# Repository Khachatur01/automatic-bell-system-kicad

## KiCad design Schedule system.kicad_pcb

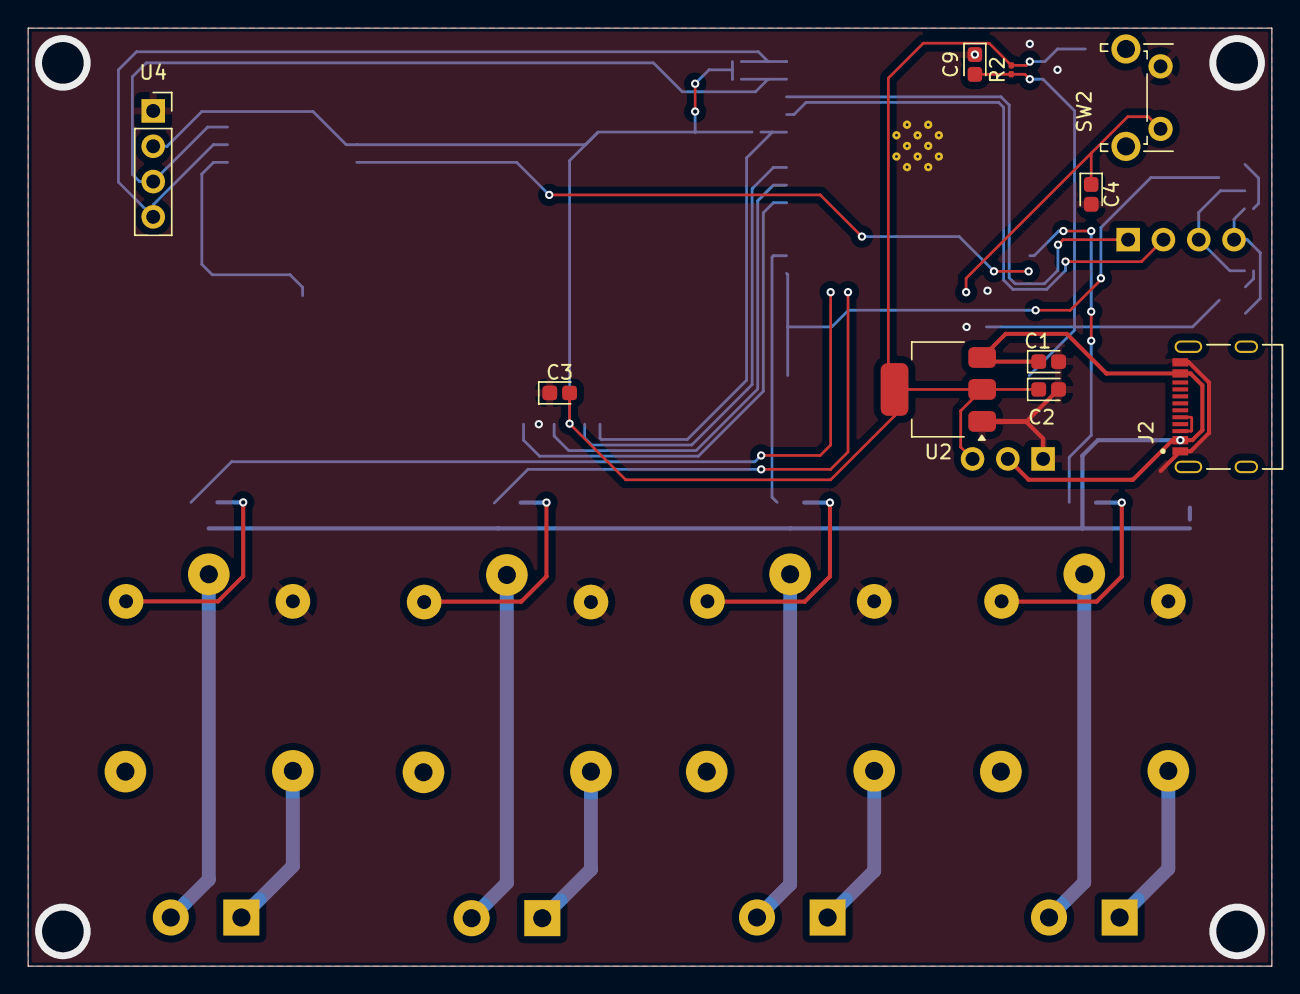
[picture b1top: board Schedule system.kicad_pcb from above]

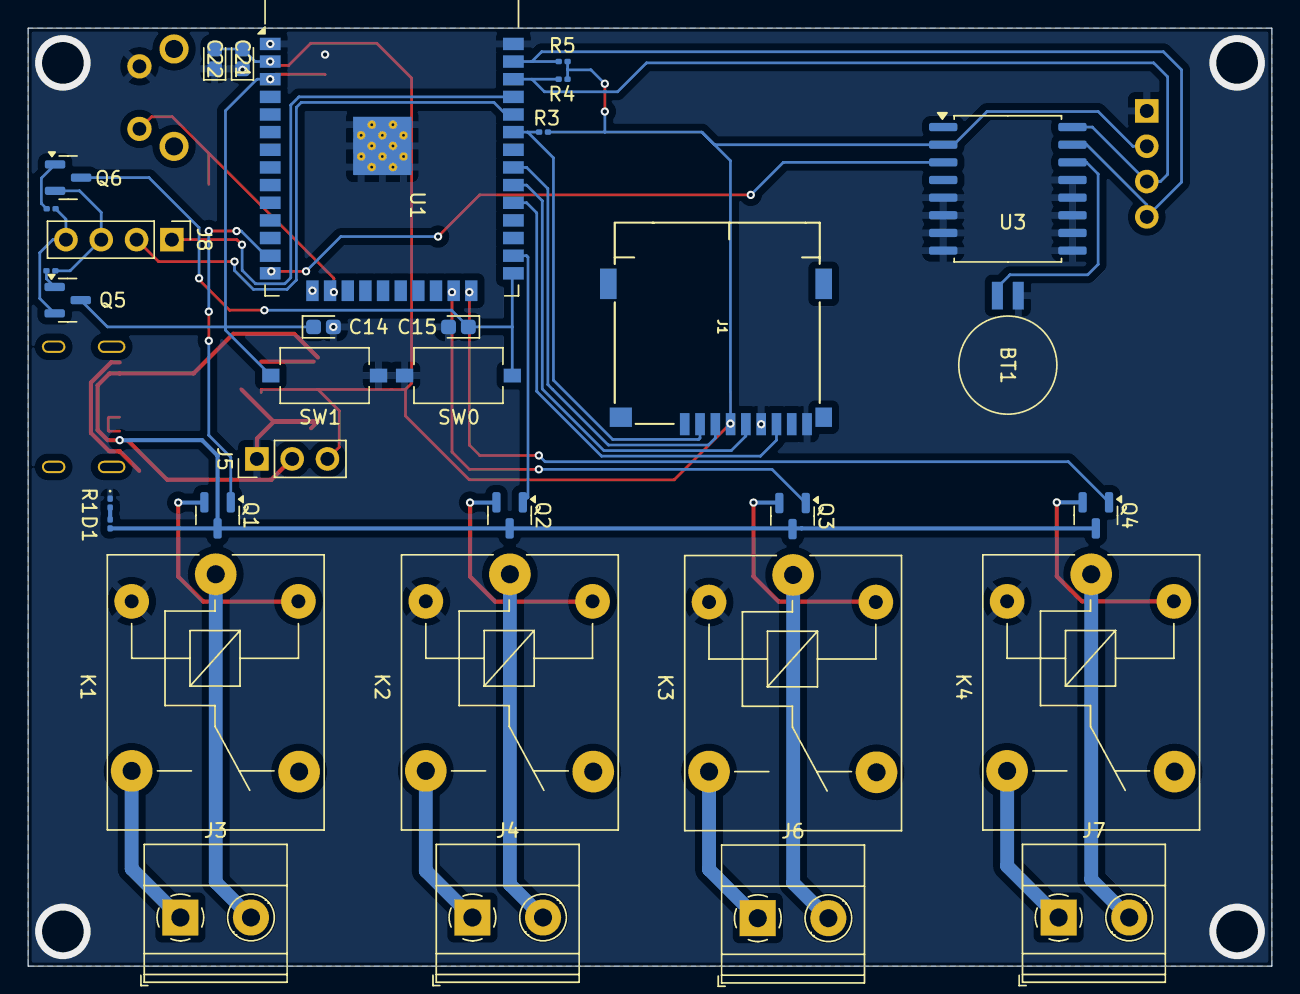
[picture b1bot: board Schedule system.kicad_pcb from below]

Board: 2 copper layers, 89.5 x 67.5 mm, 43 parts (33 on the bottom side), 37 nets.

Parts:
BT1: Battery_Cell; BatteryHolder_Seiko_MS621F
C1, C2, C3, C21, C22: 22uF/10V(20%); CP_EIA-1608-08_AVX-J
C4, C9, C14: 0.1uF/50V(10%); CP_EIA-1608-08_AVX-J
C15: 0.1uF/50V(10%)(NC); CP_EIA-1608-08_AVX-J
D1: RED LED; LED_0201_0603Metric
J1: MicroSd Card Socket; J_SD_Card-micro_socket_A
J2: USB Type-C Power; HRO_TYPE-C-31-M-12
J3: Screw Terminal 0; TerminalBlock_Phoenix_MKDS-1,5-2-5.08_1x02_P5.08mm_Horizont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
J4, J6, J7: Screw Terminal 1; TerminalBlock_Phoenix_MKDS-1,5-2-5.08_1x02_P5.08mm_Horizont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
J5: Power Interface; PinHeader_1x03_P2.54mm_Vertical
J8: UART Programming Interface; PinHeader_1x04_P2.54mm_Vertical
K1, K2, K3, K4: 220V/5V; Relay_SPDT_SANYOU_SRD_Series_Form_C
Q1, Q2, Q3, Q4, Q5, Q6: SS8050; SOT-23
R1: 2k(5%); R_0201_0603Metric
R2: 10k(5%); R_0201_0603Metric
R3: 10K; R_0201_0603Metric
R4, R5: 4.7K; R_0201_0603Metric
R6, R7: 10K (5%); R_0201_0603Metric
SW0: IO0; SW_Tactile_SPST_NO_Straight_CK_PTS636Sx25SMTRLFS
SW1: EN; SW_Tactile_SPST_NO_Straight_CK_PTS636Sx25SMTRLFS
SW2: RESET_PASSWORDS; SW_Tactile_SPST_Angled_PTS645Vx31-2LFS
U1: ESP32-WROOM-32
U2: AMS1117-3.3; SOT-223-3_TabPin2
U3: DS3231M; SOIC-16W_7.5x10.3mm_P1.27mm
U4: DM-OLED096-636; PinSocket_1x04_P2.54mm_Vertical

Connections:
/ALARM_OUTPUT_0: Q1.1 (B), U1.13 (IO14)
/ALARM_OUTPUT_1: Q2.1 (B), U1.26 (IO4)
/ALARM_OUTPUT_2: Q3.1 (B), U1.23 (IO15)
/ALARM_OUTPUT_3: Q4.1 (B), U1.24 (IO2)
/CLOCK_INT/SQW: U1.14 (IO12), U3.3 (~INT/SQW)
/DTR: J8.3, Q6.2 (E), R6.1
/EN: C9.2, C14.1, Q5.3 (C), R2.2, SW1.2, U1.3 (EN)
/EXT_5V: C1.1, J2.A4_B9 (VBUS), J2.B4_A9 (VBUS), J5.2, Q1.3 (C), Q2.3 (C), Q3.3 (C), Q4.3 (C), R1.2, U2.3 (VI)
/I2C_SCL: R4.2, U1.36 (IO22), U3.16 (SCL), U4.3 (SCL)
/I2C_SDA: R5.2, U1.37 (IO23), U3.15 (SDA), U4.4 (SDA)
/IO0: C15.1, Q6.3 (C), SW0.2, U1.25 (IO0)
/RESET_PASSWORD: C4.1, SW2.2, U1.16 (IO13)
/RTS: J8.4, Q5.2 (E), R7.1
/RXD0: J8.2, U1.34 (RXD0/IO3)
/SD_SPI_CS: J1.2 (DAT3/CD), R3.2, U1.33 (IO21)
/SPI_MISO: J1.7 (DAT0), U1.29 (IO5)
/SPI_MOSI: J1.3 (CMD), U1.31 (IO19)
/SPI_SCK: J1.5 (CLK), U1.30 (IO18)
/TXD0: J8.1, U1.35 (TXD0/IO1)
/VDD33: C2.1, C3.2, C21.2, C22.2, J1.4 (VDD), J5.3, R2.1, R3.1, R4.1, R5.1, U1.2 (VDD), U2.2 (VO), U3.2 (VCC), U4.2 (VCC_IN)
GND: BT1.2 (-), C1.2, C2.2, C3.1, C4.2, C9.1, C14.2, C15.2, C21.1, C22.1, D1.1 (K), J1.6 (VSS), J1.9 (SHIELD), J2.A1_B12 (GND), J2.B1_A12 (GND), J5.1, K1.2, K2.2, K3.2, K4.2, SW0.1, SW1.1, SW2.1, U1.1 (GND), U1.15 (GND), U1.38 (GND), U1.39 (GND), U2.1 (GND), U3.5 (GND), U3.6 (GND), U3.7 (GND), U3.8 (GND), U3.9 (GND), U3.10 (GND), U3.11 (GND), U3.12 (GND), U3.13 (GND), U4.1 (GND)
unnamed: BT1.1 (+), U3.14 (VBAT)
unnamed: D1.2 (A), R1.1
unnamed: J3.1, K1.3
unnamed: J3.2, K1.1
unnamed: J4.1, K2.3
unnamed: J4.2, K2.1
unnamed: J6.1, K3.3
unnamed: J6.2, K3.1
unnamed: J7.1, K4.3
unnamed: J7.2, K4.1
unnamed: K1.5, Q1.2 (E)
unnamed: K2.5, Q2.2 (E)
unnamed: K3.5, Q3.2 (E)
unnamed: K4.5, Q4.2 (E)
unnamed: Q5.1 (B), R6.2
unnamed: Q6.1 (B), R7.2

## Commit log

2025-04-06 Remove unnecessary files.
